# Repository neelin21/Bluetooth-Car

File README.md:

## Robot

# To Do
  1. Program the Controller
  2. Finish Bluetooth and message code
  3. Test Controller
  4. Design Controller case
  5. Finish multithreading code
  6. Finish Robot Body

# Scope:

  This project will be comprised of a robot that will be able to perform various functions and a remote control that will initially control the robot. The robot will be able to communicate with an individual and answer questions and making conversations. This "intelligence" will begin in the form of a basic chat bot and will become more advanced as the project continues. The remote will being as a main source control for the robot. As the robots intelligence increases, the remote will become less used and more of a manual override.
  
  The remote will have two PSP joysticks in order to control movement and body rotation. There will also be four tactile buttons that will be able to signal certain functions and actions. These functions will be determined based on need and possible debugging needs. The signals will be sent to the robot over bluetooth. The remote will have a bluetooth module in order to send these commands to the robot. 
  
  The robot will able to communicate with the user using a microphone and speacker. The audio recorded by microphone will be analyzed by a Raspberry Pi Zero W and converted to text then a response will be formed and outputed by the Raspberry Pi Zero W. Currently the bluetooth module in the Raspberry Pi made this a great choice for the controller of the robot. 
  
# Overview:
(More indepth review)

# Hardware:
(Overview of hardware used)

# Test Process:

# Software:

# Conclusion:

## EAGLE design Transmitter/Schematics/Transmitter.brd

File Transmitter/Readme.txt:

Overview:
(More indepth review)
  This trnasmitter will communicate with a robot using bluetooth. This remote will send signals to the robot, which will trigger certain functions. 

Hardware:
(Overview of hardware used)
  Material:
  (List of material)
  1x ATtiny 84
  2x 1uF Ceramic Capacitor
  4x 10uF Ceramic Capacitor
  1x 22uF Ceramic Capacitor
  1x 27uF Ceramic Capacitor
  1x 100uF Ceramic Capacitor
  2x Diode 1N5818
  1x Inductor CLS62SMD
  2x Joysticks PSP
  1x LT1930ES5SMD
  2x 85 Threw-Hole Resisitor
  5x 10K Threw-Hole Resisitor
  1x 13.3K Threw-Hole Resisitor
  1x 21.5K Threw-Hole Resisitor
  1x Switch
  4x Tactile Button
  2x 5mm LED
  1x 2 Pin Header
  
Test Process:

Software:

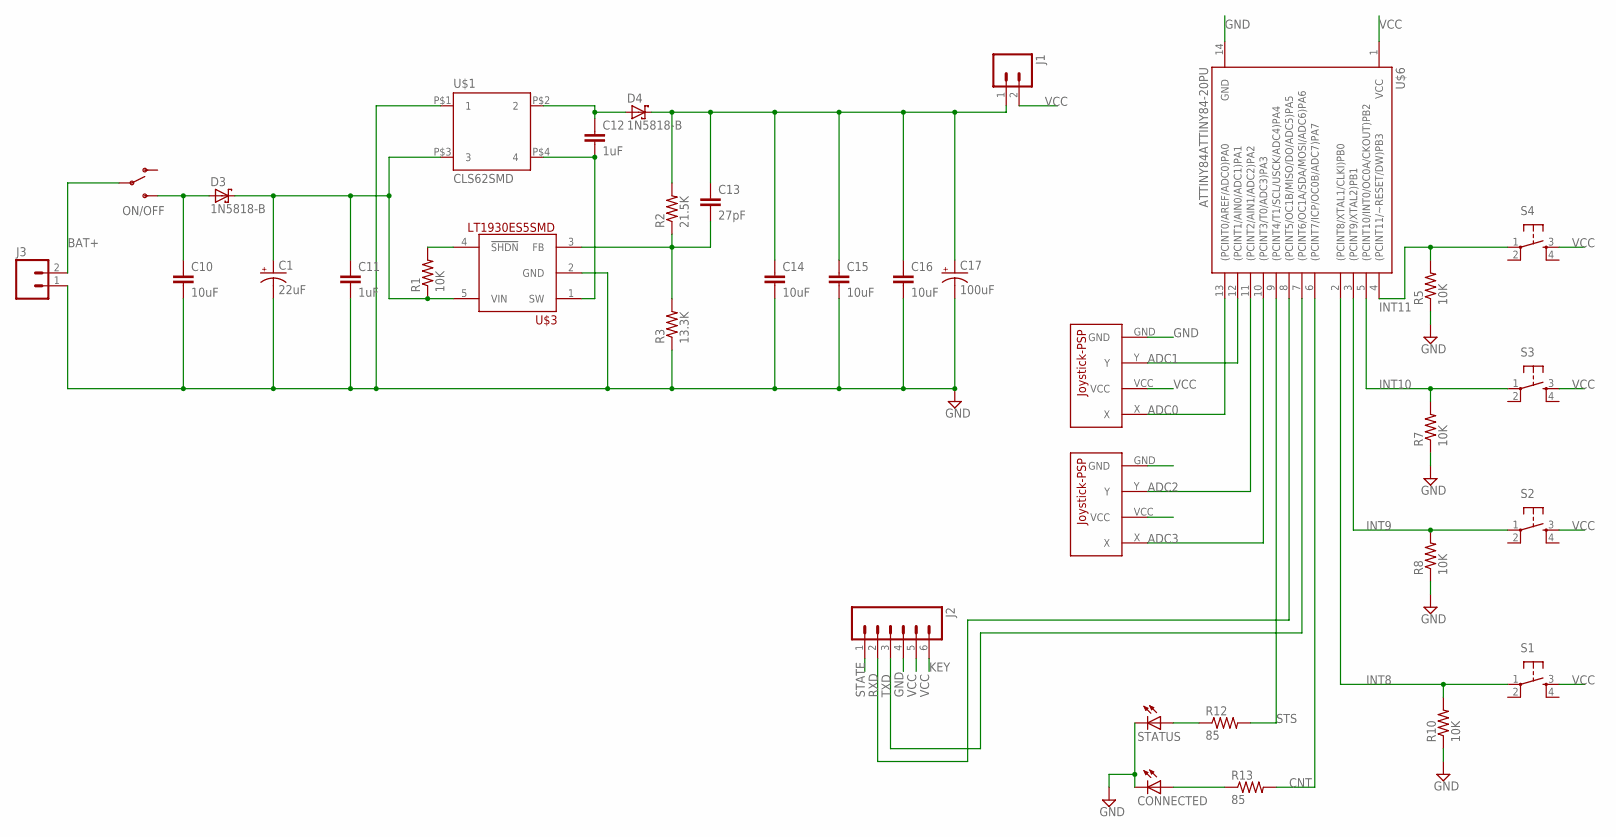
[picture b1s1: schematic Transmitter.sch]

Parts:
C1: 22uF; CPOL-RADIAL-10UF-25V; MPN MKS2B042201F00KSSD
C10, C14, C15, C16: 10uF; CAP-PTH-SMALLEZ
C11, C12: 1uF; CAP-PTH-SMALLEZ
C13: 27pF; CAP-PTH-SMALLEZ
C17: 100uF; CPOL-RADIAL-10UF-25V
CONNECTED: LED5MM
D3, D4: 1N5818-B; DO41-7.6
J1: M02PTH; 1X02
J2: M06NO_SILK_FEMALE_PTH; 1X06_NO_SILK
J3: M021X02_NO_SILK; 1X02_NO_SILK
ON/OFF: SWITCH-SPDTKIT; SWITCH-SPDT_KIT
R1, R5, R7, R8, R10: 10K; AXIAL-0.4
R2: 21.5K; AXIAL-0.4
R3: 13.3K; AXIAL-0.4
R12, R13: 85; AXIAL-0.4
S1, S2, S3, S4: TAC_SWITCHPTH; TACTILE-PTH
STATUS: LED5MM
U$1: CLS62SMD; CLS62
U$2, U$5: JOYSTICK-PSP1000
U$3: LT1930ES5SMD; LT1930ES5
U$6: ATTINY84ATTINY84-20PU; DIL14

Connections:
ADC0: U$2.X, U$6.13 ((PCINT0/AREF/ADC0)PA0)
ADC1: U$2.Y, U$6.12 ((PCINT1/AIN0/ADC1)PA1)
ADC2: U$5.Y, U$6.11 ((PCINT2/AIN1/ADC2)PA2)
ADC3: U$5.X, U$6.10 ((PCINT3/T0/ADC3)PA3)
BAT+: J3.2, ON/OFF.2
CNT: R13.P$2 (2), U$6.6 ((PCINT7/ICP/OC0B/ADC7)PA7)
GND: C1.2 (-), C10.2, C11.2, C14.2, C15.2, C16.2, C17.2 (-), CONNECTED.K (C), J2.4, J3.1, R3.P$1 (1), R5.P$1 (1), R7.P$1 (1), R8.P$1 (1), R10.P$1 (1), STATUS.K (C), U$1.P$1 (1), U$2.GND, U$3.2 (GND), U$5.GND, U$6.14 (GND)
INT8: R10.P$2 (2), S1.1, U$6.2 ((PCINT8/XTAL1/CLKI)PB0)
INT9: R8.P$2 (2), S2.1, U$6.3 ((PCINT9/XTAL2)PB1)
INT10: R7.P$2 (2), S3.1, U$6.5 ((PCINT10/INT0/OC0A/CKOUT)PB2)
INT11: R5.P$2 (2), S4.1, U$6.4 ((PCINT11/~RESET/DW)PB3)
unnamed: C10.1, D3.A, ON/OFF.3 (S)
unnamed: C1.1 (+), C11.1, D3.C, R1.P$1 (1), U$1.P$3 (3), U$3.5 (VIN)
unnamed: C12.1, D4.A, U$1.P$2 (2)
unnamed: C12.2, U$1.P$4 (4), U$3.1 (SW)
unnamed: R1.P$2 (2), U$3.4 (!SHDN)
unnamed: C13.2, R2.P$1 (1), R3.P$2 (2), U$3.3 (FB)
unnamed: C13.1, C14.1, C15.1, C16.1, C17.1 (+), D4.C, J1.1, R2.P$2 (2)
unnamed: R12.P$1 (1), STATUS.A
unnamed: CONNECTED.A, R13.P$1 (1)
RXD: J2.2, U$6.8 ((PCINT5/OC1B/MISO/DO/ADC5)PA5)
STATE: J2.1
STS: R12.P$2 (2), U$6.9 ((PCINT4/T1/SCL/USCK/ADC4)PA4)
TXD: J2.3, U$6.7 ((PCINT6/OC1A/SDA/MOSI/ADC6)PA6)
VCC: J1.2, J2.5, J2.6, S1.3, S2.3, S3.3, S4.3, U$2.VCC, U$5.VCC, U$6.1 (VCC)

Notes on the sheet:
KEY

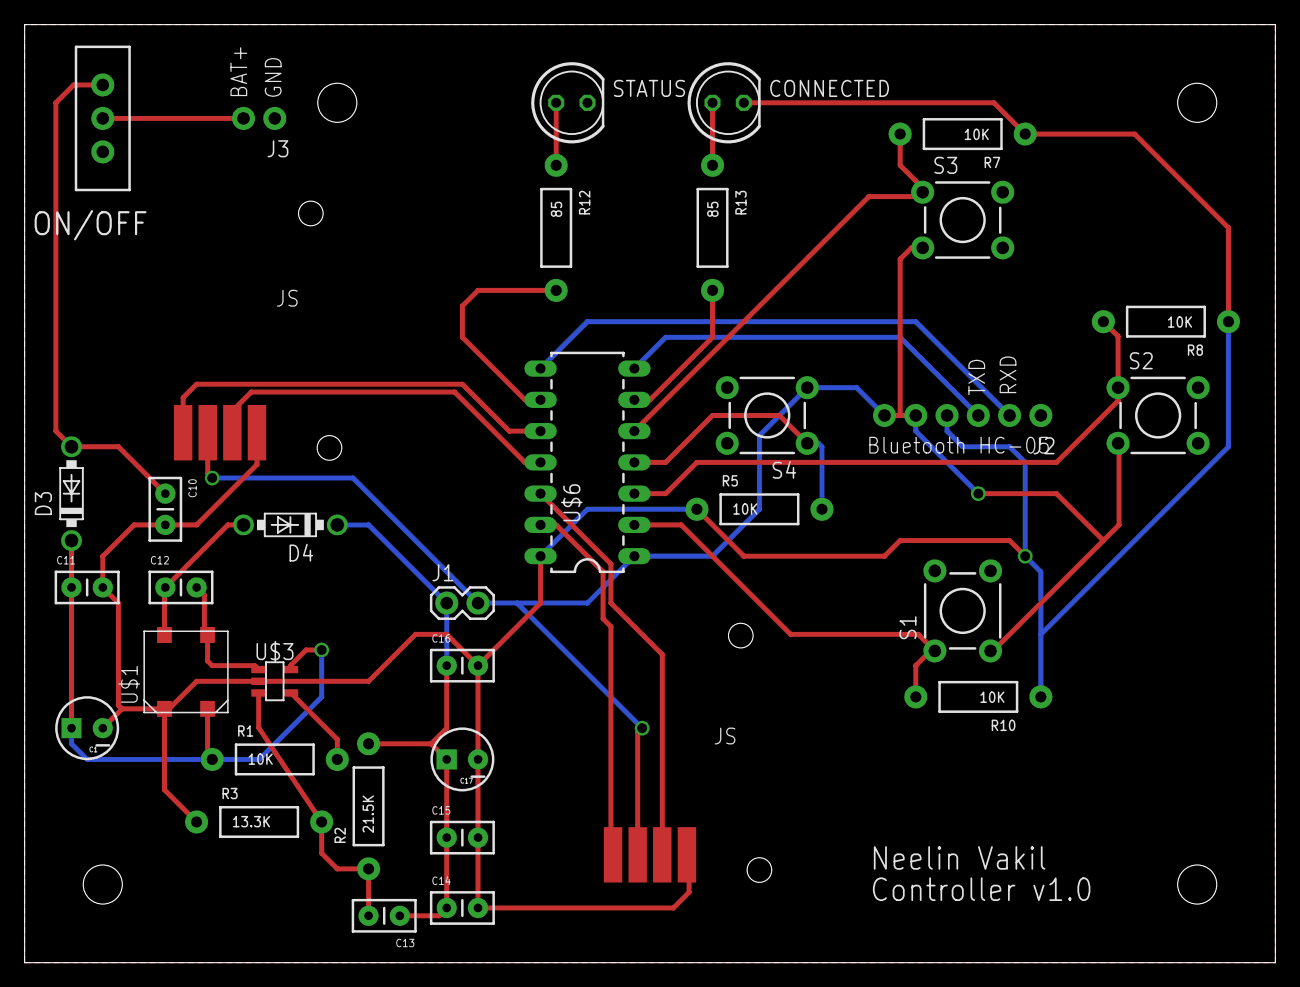
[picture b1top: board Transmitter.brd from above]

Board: 2 copper layers, 101.6 x 76.2 mm, 35 parts (0 on the bottom side), 24 nets.

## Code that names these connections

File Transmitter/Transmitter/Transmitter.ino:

/*
Pin - Ports
1 - VCC
2 - PB0
3 - PB1
4 - PB3
5 - PB2
6 - PA7
7 - PA6
8 - PA5
9 - PA4
10 - PA3
11 - PA2
12 - PA1
13 - PA0
14 - GND
*/

/*
  Message Format:
  Form: .__-#
  .CW-#
  .CC-#
  .FO-#
  .RE-#
  .FL-#
  .FR-#
  .RL-#
  .RR-#
  .FU-#
*/
char BluetoothMessage[4];

void setup()
{
  //initialize pins and interrupts
  InitButtons();
  InitADC();
  InitLEDs();
  InitBluetooth();
  
}

void loop()
{
  // put your main code here, to run repeatedly:

}

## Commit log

2017-03-03 Add files via upload
    Added starting blocks to the Artificial Intelligence aspect.
2017-03-03 Add files via upload
    Added pyAIML and AIML_Files directories to the project
2017-03-12 Rename READ_ME.txt to Readme.txt
2017-03-19 Removed unnecessary headings
2017-03-19 Created readme.txt
    An overall documentation of the project
2017-03-19 Removed unecessary sections
2017-03-19 Updated file to replace reamme.txt
2017-03-19 Updated readme.md
    Added information to the scope section
2017-03-23 Add files via upload
    Added file to handle Bluetooth inputs with motor movement
2017-03-23 Add files via upload
    Added schematics
2017-03-23 Added Speech Synthesis and readme file
2017-03-25 Added Serial and message handling code
2017-03-27 Added file to handle creating threads for the system
2017-03-28 Added To Do list
2017-03-28 Added transmitter arduino code
2017-04-01 Added schematic pdf
2017-04-01 Moved Schematic pdf
2017-04-01 Added initialization code
2017-04-04 Added interrupts, and Bluetooth Command structure
2018-03-18 Reformatted the folder structure
    Moved around some files to better organize the Raspberry Pi code and
    the WiPy code.
2018-03-18 Added WiPy Code
    Adding support for the various functions that the breakout board
    supports.
2018-03-18 Added code to Motor class
    Added functions to control the motors based off the breakout board
    configuration.
2018-03-18 Added classes for Analogs
    Created input and output classes and made the initializations for each.
    Functions will be added later based on their use.
2018-03-18 Added I2C code
    Added basic setup for I2C communication. Functions will later be added
    based on connected devices.

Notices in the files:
parts and their libraries:
SparkFun-Passives: Licensing: Creative Commons ShareAlike 4.0 International - https://creativecommons.org/licenses/by-sa/4.0
